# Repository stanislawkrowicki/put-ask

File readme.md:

# 🛠️ PepeBoy

**Portable GameBoy style console. Based on ESP32 microprocessor, 2.8" TFT display, WiFi** 

---

## 📌 Table of Contents
- [🎯 Project Goal](#-project-goal)
- [🔧 Hardware Design](#-hardware-design)
- [💻 Usage](#-usage)
- [🔧 Execution REV1](#-execution)

---

## 🎯 Project Goal

Portable and pocket size console, able to load games from external sd card. Possibility of on-line gameplay via Wi-Fi. Custom PCB board, self-made using CNC milling and UV solder mask paint; 3D printed case.

## 🔧 Hardware Design
The PCB was designed to be produced using a double-sided FR4 PCB blank. Unfortunately, due to the process, every via had to be soldered using copper wire. 

### ESP32 pinout description
#### buttons 
| Button      | Switch id | GPIO  |
|:-----------:|:------:|:-----:|
| Right Button| SW_7   | IO35  |
| Left Button | SW_5   | IO27  |
| Up Button   | SW_4   | IO33  |
| Down Button | SW_6   | IO34  |
| A Button    | SW_8   | IO14  |
| B Button    | SW_3   | IO32  |

#### touch 

| Touch Signal  | Description          | GPIO  |
|:----------:|:--------------------:|:-----:|
| MISO       | Master In Slave Out   | IO19  |
| MOSI       | Master Out Slave In   | IO23  |
| CLK        | Clock                 | IO18  |
| CS_T       | Chip Select           | IO4   |
| T_IRQ      | Interrupt Handling    | IO13  |

#### display
| Display Signal | GPIO  | Description                          |
|:--------------:|:-----:|:-------------------------------------:|
| SPI_CS         | IO21  | Display Chip Select                  |
| SPI_MOSI       | IO23  | Master Out Slave In (data)           |
| SPI_MISO       | IO19  | Master In Slave Out (data)           |
| SPI_CLK        | IO18  | Clock signal                         |
| D_DC           | IO16  | Data/Command control                 |
| D_RST          | IO17  | Display reset signal                 |
| D_LED          | IO22  | Display backlight control            |
#### SD card

| SD Signal  | GPIO  | Description                 |
|:----------:|:-----:|:---------------------------:|
| SD_CS      | IO25  | Chip Select karty SD        |
| SD_CLK     | IO18  | Clock signal                |
| SD_MISO    | IO19  | Master In Slave Out (data)  |
| SD_MOSI    | IO23  | Master Out Slave In (data)  |

#### onePixel 2x2 led matrix
|2x2 LED signal|GPIO|Description|
|:--:|:--:|:--:|
|LED_DIN| IO26|Data in|

####  general SPI
| SPI Signal | GPIO  |
|:----------:|:-----:|
| MISO       | IO19  |
| MOSI       | IO23  |
| CLK        | IO18  |

<!--  -->

### Power Management Unit (IP5306) 
#### read execution paragraph !!!!
The console can be powered remotely using, for example, a 18650 Li-ion battery. Plugging the console into external power through USB-C will power the device and charge the battery. The IP5306 is used according to the typical application from the [datasheet](https://www.datasheetcafe.com/wp-content/uploads/2020/07/IP5306.pdf). We used a one-LED configuration and skipped the KEY_LED (D5 on the datasheet).

## 💻 Usage

Description of how to use the project, e.g., how to start it, available modes, etc.

## 🔧 Execution
The PCB has been *mostly* successfully produced. We will leave a few notes describing our conclusions about what went wrong and what met or exceeded our expectations.

- Power Management Unit Failure: To be honest, I still don’t know exactly what went wrong. The design followed the datasheet, but the IC consistently failed, producing enough heat to desolder itself. After several attempts and considering the project deadline, I abandoned the idea of a remote power supply. If I were to do this again, I’d design a separate board dedicated solely to power management.

- Input-Only Pins (IO35, IO34): These pins lack internal pull-up resistors, and I neglected to include external ones in the design.

- WS2812 Segment Issue: This one’s due to a simple oversight: the collector of the Q1 transistor isn’t pulled up to 5V, which prevents proper operation of the LED segment.

- USB-C Port Soldering Difficulty: The mounting pads for the USB-C connector are too small, making the socket difficult to solder reliably. Larger pads would have made assembly easier.

---

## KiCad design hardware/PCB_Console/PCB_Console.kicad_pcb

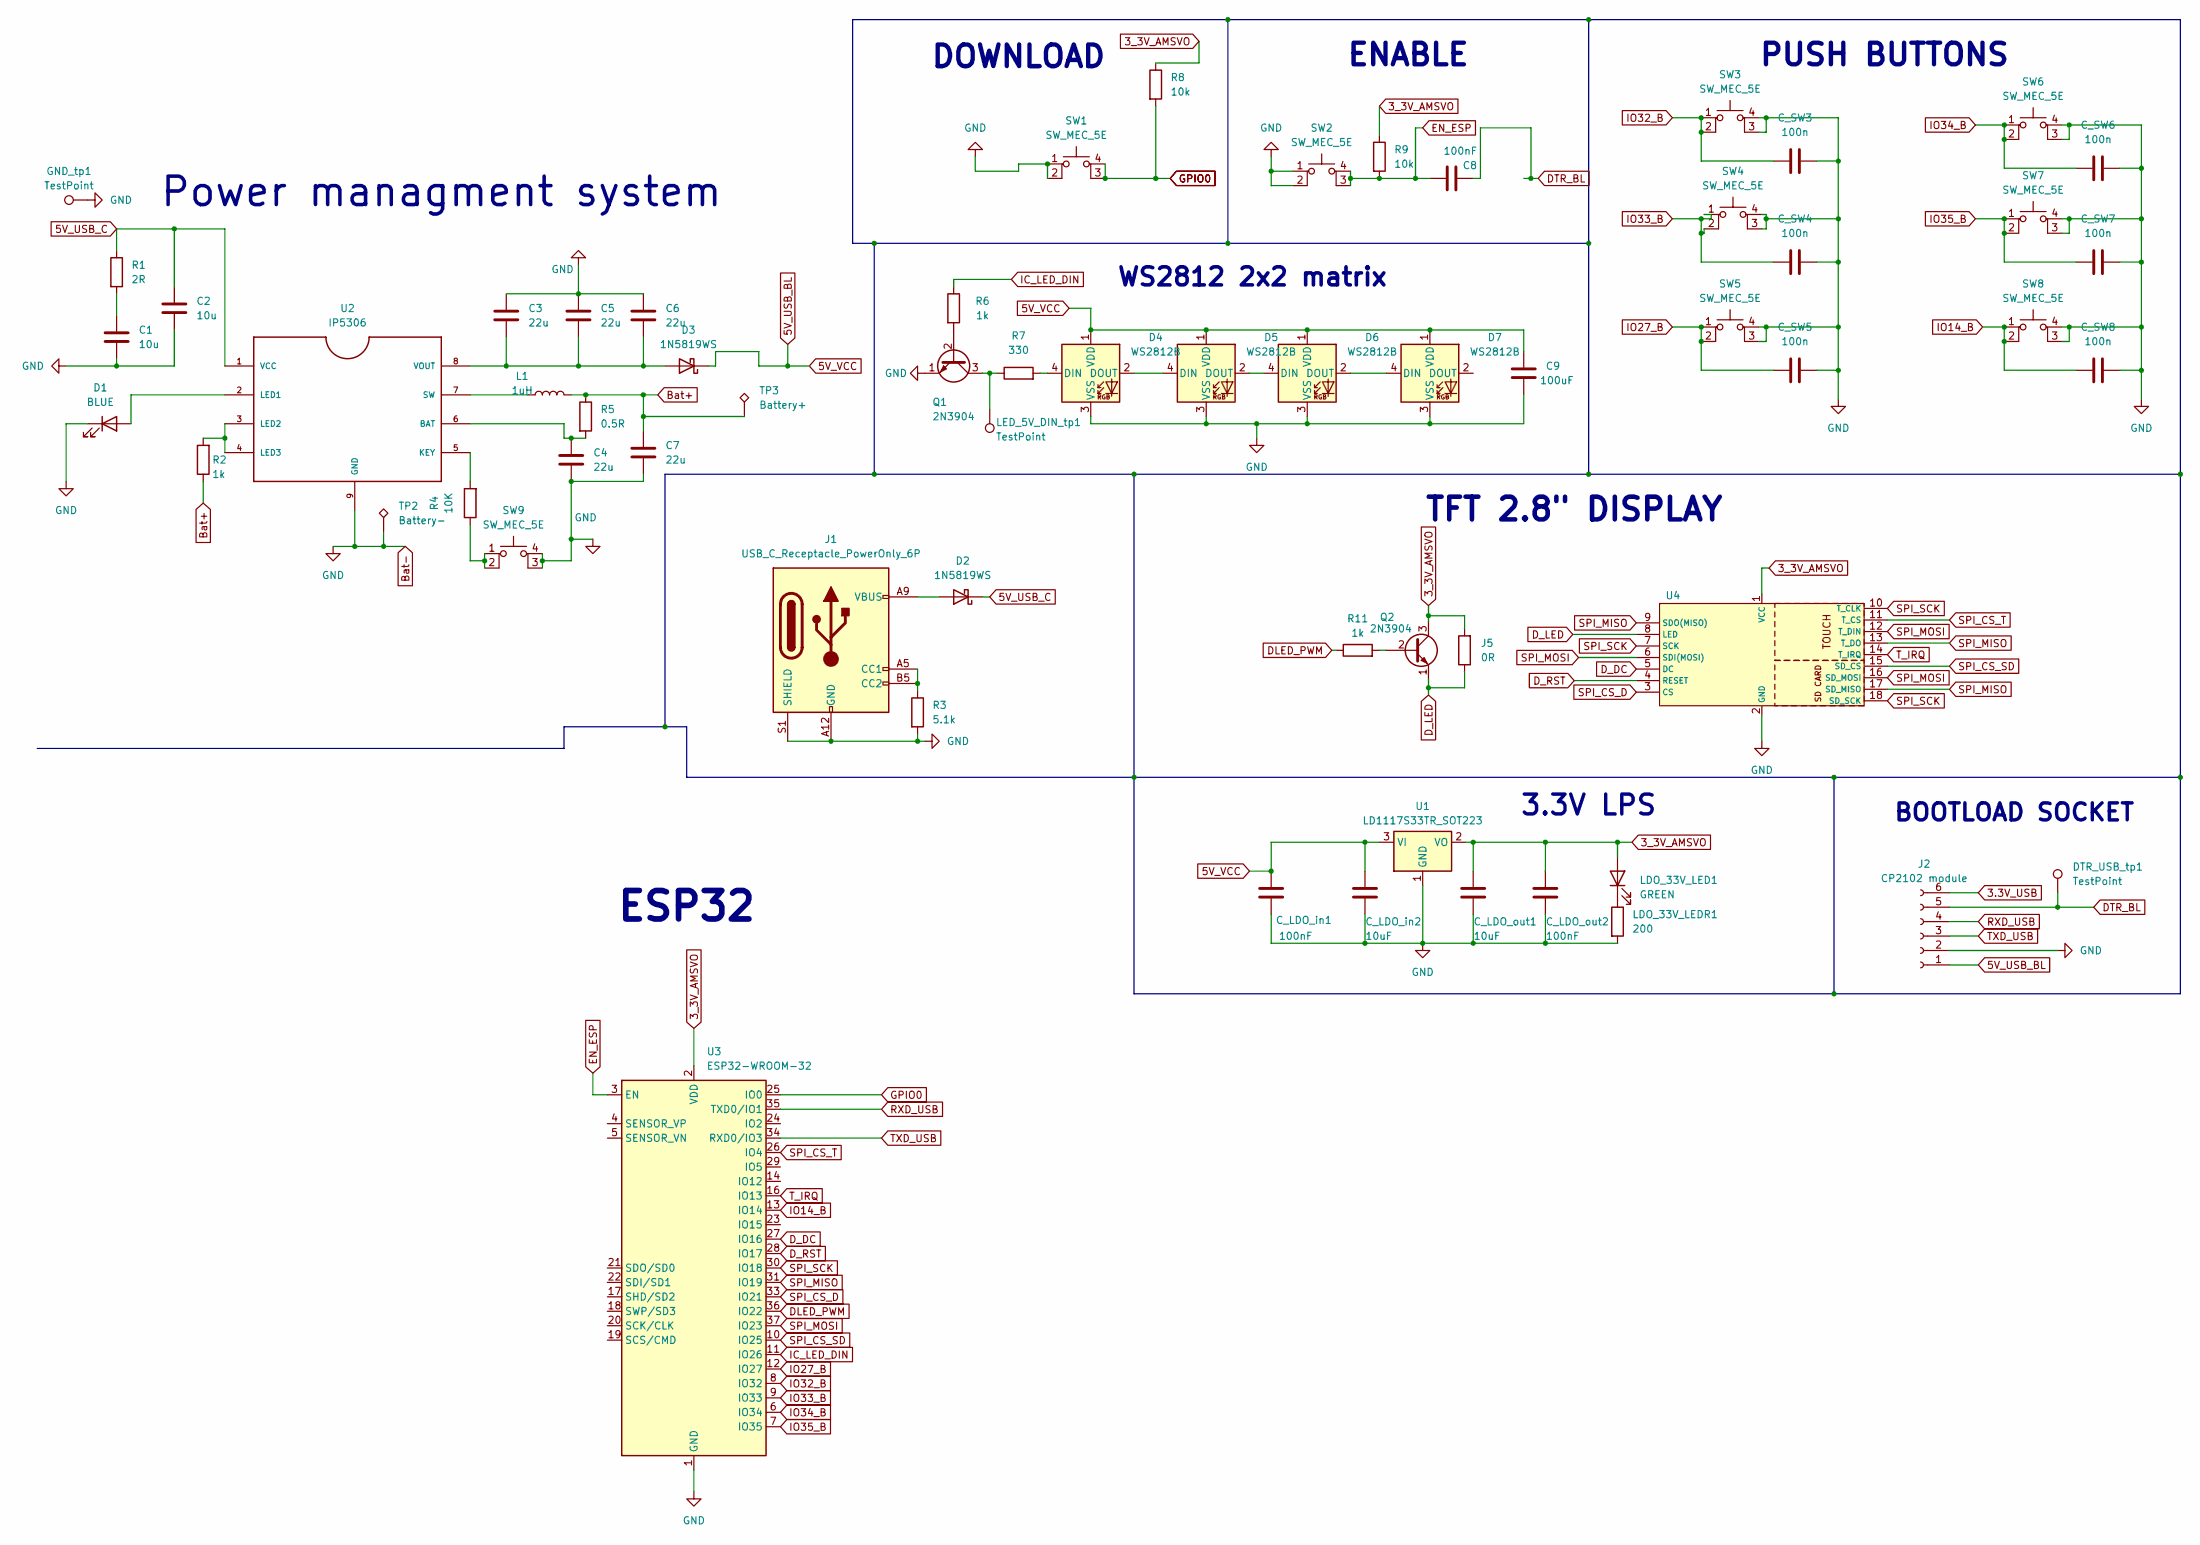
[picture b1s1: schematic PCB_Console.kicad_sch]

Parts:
C1, C2: 10u; C_1206_3216Metric_Pad1.33x1.80mm_HandSolder
C3, C4, C5, C6, C7: 22u; C_1206_3216Metric_Pad1.33x1.80mm_HandSolder
C8: 100nF; C_1206_3216Metric_Pad1.33x1.80mm_HandSolder
C9: 100uF; C_1206_3216Metric_Pad1.33x1.80mm_HandSolder
C_LDO_in1: 100nF; C_1206_3216Metric_Pad1.33x1.80mm_HandSolder
C_LDO_in2: 10uF; C_1206_3216Metric_Pad1.33x1.80mm_HandSolder
C_LDO_out1: 10uF; C_1206_3216Metric_Pad1.33x1.80mm_HandSolder
C_LDO_out2: 100nF; C_1206_3216Metric_Pad1.33x1.80mm_HandSolder
C_SW3, C_SW4, C_SW5, C_SW6, C_SW7, C_SW8: 100n; C_1206_3216Metric_Pad1.33x1.80mm_HandSolder
D1: BLUE; LED_D5.0mm
D2, D3: 1N5819WS; D_0805_2012Metric_Pad1.15x1.40mm_HandSolder
D4, D5, D6, D7: WS2812B; LED_WS2812B_PLCC4_5.0x5.0mm_P3.2mm
DTR_USB_tp1: TestPoint; TestPoint_Pad_D1.0mm
GND_tp1: TestPoint; TestPoint_Pad_D1.5mm
J1: USB_C_Receptacle_PowerOnly_6P; USB_C_Receptacle_GCT_USB4125-xx-x-0190_6P_TopMnt_Horizontal
J2: CP2102 module; PinSocket_1x06_P2.54mm_Vertical
J5: 0R; R_1206_3216Metric_Pad1.30x1.75mm_HandSolder
L1: 1uH; L_Chilisin_BMRB00060650
LDO_33V_LED1: GREEN; LED_D3.0mm
LDO_33V_LEDR1: 200; R_1206_3216Metric_Pad1.30x1.75mm_HandSolder
LED_5V_DIN_tp1: TestPoint; TestPoint_Pad_D1.0mm
Q1, Q2: 2N3904; TO-92_Wide
R1: 2R; R_1206_3216Metric_Pad1.30x1.75mm_HandSolder
R2, R6, R11: 1k; R_1206_3216Metric_Pad1.30x1.75mm_HandSolder
R3: 5.1k; R_1206_3216Metric_Pad1.30x1.75mm_HandSolder
R4: 10K; R_1206_3216Metric_Pad1.30x1.75mm_HandSolder
R5: 0.5R; R_1206_3216Metric_Pad1.30x1.75mm_HandSolder
R7: 330; R_1206_3216Metric_Pad1.30x1.75mm_HandSolder
R8, R9: 10k; R_1206_3216Metric_Pad1.30x1.75mm_HandSolder
SW1, SW2, SW9: SW_MEC_5E; SW_TS04-66-95-BK-100-SMT
SW3, SW4, SW5, SW6, SW7, SW8: SW_MEC_5E; SW_Push_12x12_aliexpress
TP2: Battery-; TestPoint_THTPad_D1.5mm_Drill0.7mm
TP3: Battery+; TestPoint_THTPad_D1.5mm_Drill0.7mm
U1: LD1117S33TR_SOT223; SOT-223-3_TabPin2
U2: IP5306; SOIC9P127_490X600X170L84X42T330X241N
U3: ESP32-WROOM-32
U4: TFT ILI9341

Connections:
3.3V_USB: J2.6
3_3V_AMSVO: C_LDO_out1.1, C_LDO_out2.1, J5.2, LDO_33V_LED1.2 (A), Q2.3 (C), R8.1, R9.1, U1.2 (VO), U3.2 (VDD), U4.1 (VCC)
5V_USB_BL: C9.2, C_LDO_in1.1, C_LDO_in2.1, D3.1 (K), D4.1 (VDD), D5.1 (VDD), D6.1 (VDD), D7.1 (VDD), J2.1, U1.3 (VI)
5V_USB_C: C2.1, D2.1 (K), R1.1, U2.1 (VCC)
Bat+: C7.1, L1.2, R2.1, R5.1, TP3.1
Bat-: C1.2, C2.2, C3.1, C4.2, C5.1, C6.1, C7.2, C9.1, C_LDO_in1.2, C_LDO_in2.2, C_LDO_out1.2, C_LDO_out2.2, C_SW3.1, C_SW4.1, C_SW5.1, C_SW6.1, C_SW7.1, C_SW8.1, D1.1 (K), D4.3 (VSS), D5.3 (VSS), D6.3 (VSS), D7.3 (VSS), GND_tp1.1, J1.A12 (GND), J1.B12 (GND), J1.S1 (SHIELD), J2.2, LDO_33V_LEDR1.2, Q1.1 (E), R3.2, SW1.1, SW1.2, SW2.1, SW2.2, SW3.3 (K), SW3.4 (A), SW4.3 (K), SW4.4 (A), SW5.3 (K), SW5.4 (A), SW6.3 (K), SW6.4 (A), SW7.3 (K), SW7.4 (A), SW8.3 (K), SW8.4 (A), SW9.3 (K), SW9.4 (A), TP2.1, U1.1 (GND), U2.9 (GND), U3.1 (GND), U3.15 (GND), U3.38 (GND), U3.39 (GND), U4.2 (GND)
DLED_PWM: R11.1, U3.36 (IO22)
DTR_BL: C8.2, DTR_USB_tp1.1, J2.5
D_DC: U3.27 (IO16), U4.5 (DC)
D_LED: J5.1, Q2.1 (E), U4.8 (LED)
D_RST: U3.28 (IO17), U4.4 (RESET)
EN_ESP: C8.1, R9.2, SW2.3 (K), SW2.4 (A), U3.3 (EN)
GPIO0: R8.2, SW1.3 (K), SW1.4 (A), U3.25 (IO0)
IC_LED_DIN: R6.1, U3.11 (IO26)
IO14_B: C_SW8.2, SW8.1, SW8.2, U3.13 (IO14)
IO27_B: C_SW5.2, SW5.1, SW5.2, U3.12 (IO27)
IO32_B: C_SW3.2, SW3.1, SW3.2, U3.8 (IO32)
IO33_B: C_SW4.2, SW4.1, SW4.2, U3.9 (IO33)
IO34_B: C_SW6.2, SW6.1, SW6.2, U3.6 (IO34)
IO35_B: C_SW7.2, SW7.1, SW7.2, U3.7 (IO35)
unnamed: C1.1, R1.2
unnamed: D1.2 (A), U2.2 (LED1)
unnamed: D2.2 (A), J1.A9 (VBUS), J1.B9 (VBUS)
unnamed: C3.2, C5.2, C6.2, D3.2 (A), U2.8 (VOUT)
unnamed: D4.4 (DIN), R7.2
unnamed: D4.2 (DOUT), D5.4 (DIN)
unnamed: D5.2 (DOUT), D6.4 (DIN)
unnamed: D6.2 (DOUT), D7.4 (DIN)
unnamed: J1.A5 (CC1), J1.B5 (CC2), R3.1
unnamed: LDO_33V_LED1.1 (K), LDO_33V_LEDR1.1
unnamed: Q1.2 (B), R6.2
unnamed: LED_5V_DIN_tp1.1, Q1.3 (C), R7.1
unnamed: Q2.2 (B), R11.2
unnamed: R4.1, SW9.1, SW9.2
unnamed: C4.1, R5.2, U2.6 (BAT)
unnamed: R4.2, U2.5 (KEY)
unnamed: R2.2, U2.3 (LED2), U2.4 (LED3)
unnamed: L1.1, U2.7 (SW)
RXD_USB: J2.4, U3.35 (TXD0/IO1)
SPI_CS_D: U3.33 (IO21), U4.3 (CS)
SPI_CS_SD: U3.10 (IO25), U4.15 (SD_CS)
SPI_CS_T: U3.26 (IO4), U4.11 (T_CS)
SPI_MISO: U3.31 (IO19), U4.9 (SDO(MISO)), U4.13 (T_DO), U4.17 (SD_MISO)
SPI_MOSI: U3.37 (IO23), U4.6 (SDI(MOSI)), U4.12 (T_DIN), U4.16 (SD_MOSI)
SPI_SCK: U3.30 (IO18), U4.7 (SCK), U4.10 (T_CLK), U4.18 (SD_SCK)
TXD_USB: J2.3, U3.34 (RXD0/IO3)
T_IRQ: U3.16 (IO13), U4.14 (T_IRQ)

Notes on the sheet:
ESP32
PUSH BUTTONS
Power managment system
BOOTLOAD SOCKET
3.3V LPS
TFT 2.8" DISPLAY
DOWNLOAD
WS2812 2x2 matrix
ENABLE

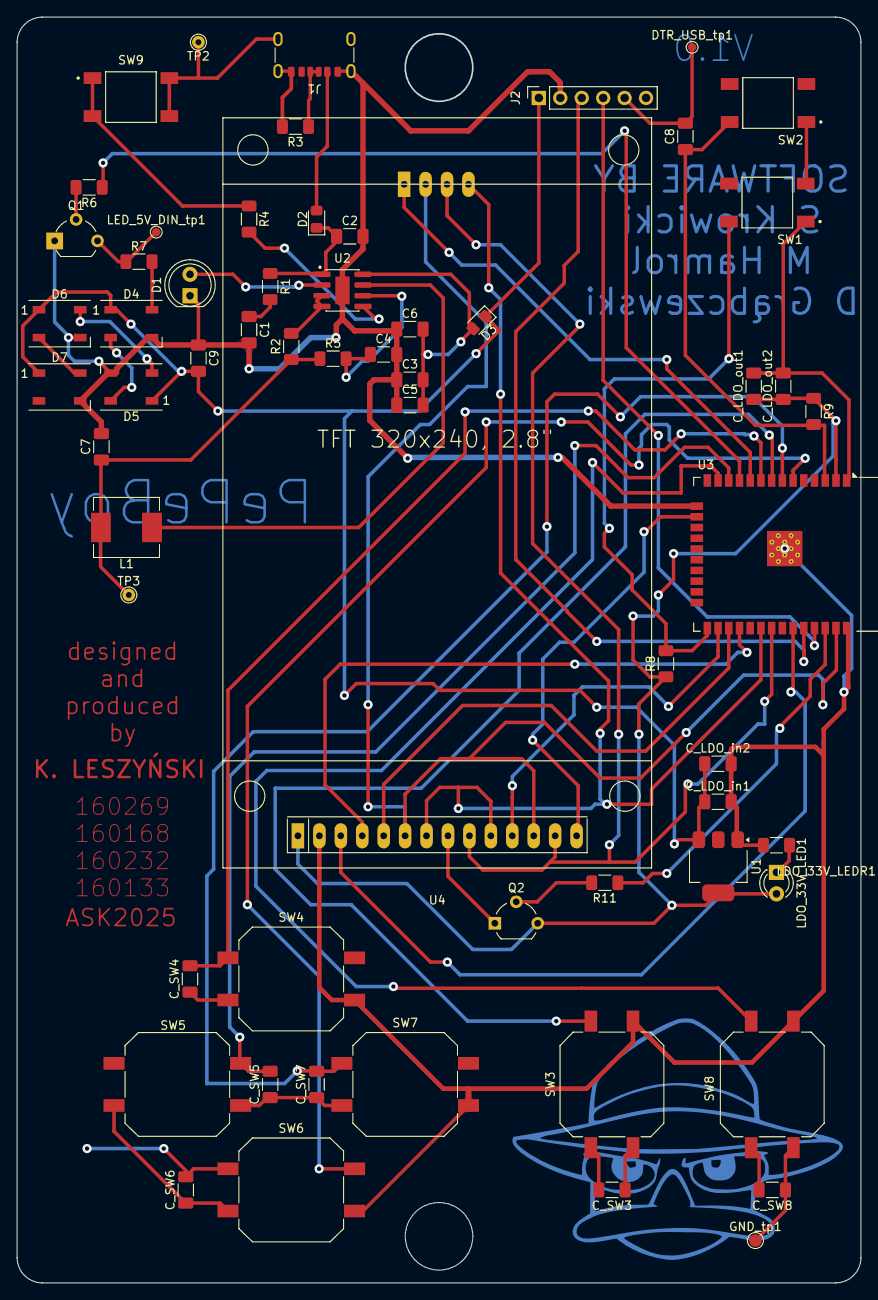
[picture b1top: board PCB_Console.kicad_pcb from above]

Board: 2 copper layers, 100.0 x 150.0 mm, 61 parts (0 on the bottom side), 46 nets.

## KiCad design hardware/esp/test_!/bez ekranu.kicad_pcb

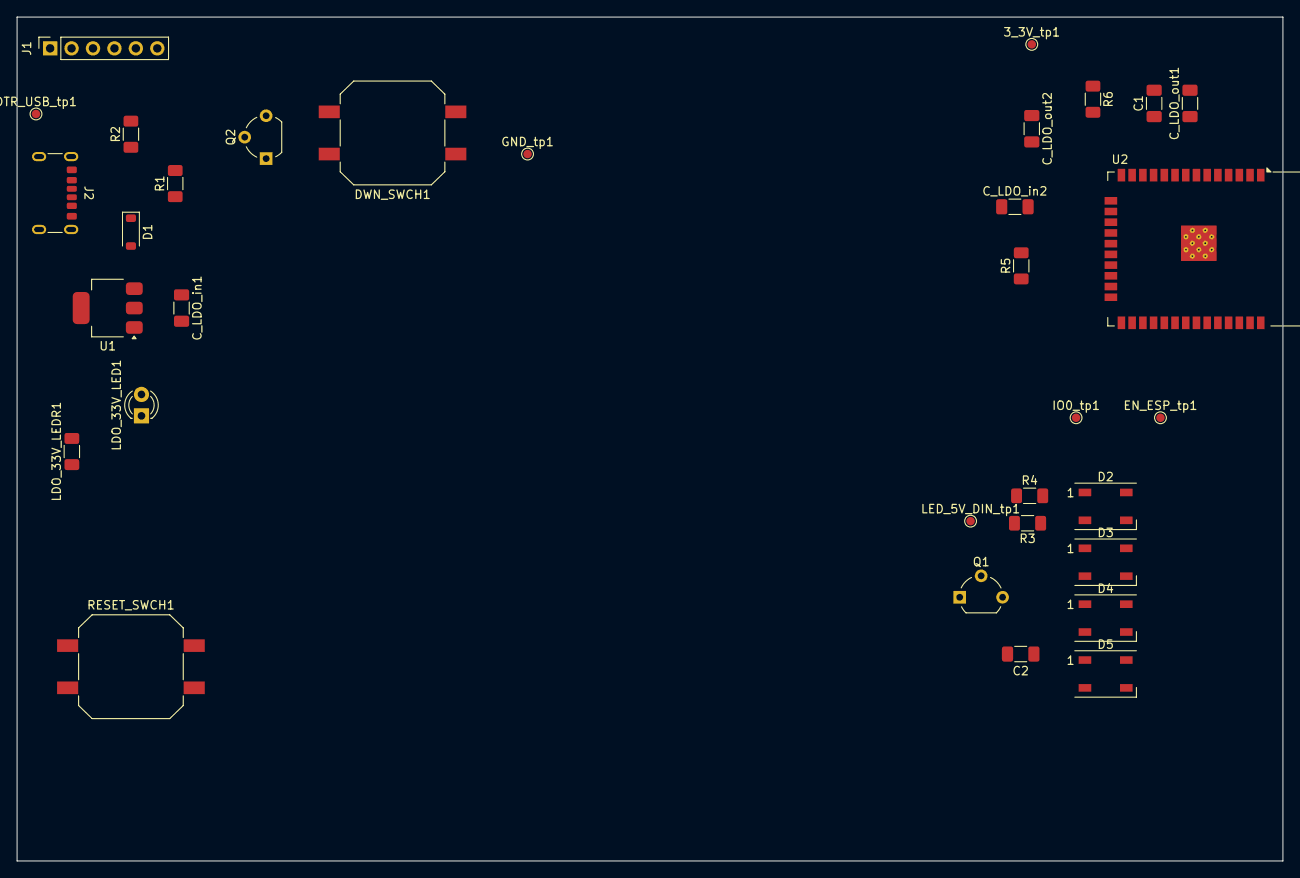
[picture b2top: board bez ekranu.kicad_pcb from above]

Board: 2 copper layers, 150.0 x 100.0 mm, 33 parts (0 on the bottom side), 17 nets, no tracks yet.

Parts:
3_3V_tp1: TestPoint; TestPoint_Pad_D1.0mm
C1: 100nF; C_1206_3216Metric_Pad1.33x1.80mm_HandSolder
C2: 100uF; C_1206_3216Metric_Pad1.33x1.80mm_HandSolder
C_LDO_in1: 100nF; C_1206_3216Metric_Pad1.33x1.80mm_HandSolder
C_LDO_in2: 10uF; C_1206_3216Metric_Pad1.33x1.80mm_HandSolder
C_LDO_out1: 10uF; C_1206_3216Metric_Pad1.33x1.80mm_HandSolder
C_LDO_out2: 100nF; C_1206_3216Metric_Pad1.33x1.80mm_HandSolder
D1: 1N5819WS; D_SOD-123
D2, D3, D4, D5: WS2812B; LED_WS2812B_PLCC4_5.0x5.0mm_P3.2mm
DTR_USB_tp1: TestPoint; TestPoint_Pad_D1.0mm
DWN_SWCH1: SW_Push_Dual; SW_Push_12x12_aliexpress
EN_ESP_tp1: TestPoint; TestPoint_Pad_D1.0mm
GND_tp1: TestPoint; TestPoint_Pad_D1.0mm
IO0_tp1: TestPoint; TestPoint_Pad_D1.0mm
J1: CP2102 module; PinSocket_1x06_P2.54mm_Vertical
J2: USB_C_Receptacle_PowerOnly_6P; USB_C_Receptacle_GCT_USB4125-xx-x-0190_6P_TopMnt_Horizontal
LDO_33V_LED1: LED; LED_D3.0mm
LDO_33V_LEDR1: 150; R_1206_3216Metric_Pad1.30x1.75mm_HandSolder
LED_5V_DIN_tp1: TestPoint; TestPoint_Pad_D1.0mm
Q1, Q2: 2N3904; TO-92_Wide
R1: 5.1k; R_1206_3216Metric_Pad1.30x1.75mm_HandSolder
R2, R3: 1k; R_1206_3216Metric_Pad1.30x1.75mm_HandSolder
R4: 330; R_1206_3216Metric_Pad1.30x1.75mm_HandSolder
R5, R6: 10k; R_1206_3216Metric_Pad1.30x1.75mm_HandSolder
RESET_SWCH1: SW_Push_Dual; SW_Push_12x12_aliexpress
U1: LD1117S33TR_SOT223; SOT-223-3_TabPin2
U2: ESP32-WROOM-32

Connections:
3_3V_AMSVO: 3_3V_tp1.1, C_LDO_out1.1, C_LDO_out2.1, LDO_33V_LED1.2 (A), R5.1, R6.1, U1.2 (VO), U2.2 (VDD)
5V_USB_BL: D1.1 (K), J1.1, J2.A9 (VBUS), J2.B9 (VBUS)
5V_VCC: C2.2, C_LDO_in1.1, C_LDO_in2.1, D1.2 (A), D2.1 (VDD), D3.1 (VDD), D4.1 (VDD), D5.1 (VDD), U1.3 (VI)
DTR_BL: C1.2, DTR_USB_tp1.1, J1.5, R2.1
EN_ESP: C1.1, EN_ESP_tp1.1, R6.2, RESET_SWCH1.2, RESET_SWCH1.4, U2.3 (EN)
GND: C2.1, C_LDO_in1.2, C_LDO_in2.2, C_LDO_out1.2, C_LDO_out2.2, D2.3 (VSS), D3.3 (VSS), D4.3 (VSS), D5.3 (VSS), DWN_SWCH1.1, DWN_SWCH1.3, GND_tp1.1, J1.2, J2.A12 (GND), J2.B12 (GND), J2.S1 (SHIELD), LDO_33V_LEDR1.2, Q1.1 (E), Q2.1 (E), R1.2, RESET_SWCH1.1, RESET_SWCH1.3, U1.1 (GND), U2.1 (GND), U2.15 (GND), U2.38 (GND), U2.39 (GND)
GPIO0: DWN_SWCH1.2, DWN_SWCH1.4, IO0_tp1.1, Q2.3 (C), R5.2, U2.25 (IO0)
IC_LED_DIN: R3.1, U2.7 (IO35), U2.27 (IO16)
unnamed: D2.4 (DIN), R4.2
unnamed: D2.2 (DOUT), D3.4 (DIN)
unnamed: D3.2 (DOUT), D4.4 (DIN)
unnamed: D4.2 (DOUT), D5.4 (DIN)
unnamed: J2.A5 (CC1), J2.B5 (CC2), R1.1
unnamed: LDO_33V_LED1.1 (K), LDO_33V_LEDR1.1
unnamed: Q1.2 (B), R3.2
unnamed: LED_5V_DIN_tp1.1, Q1.3 (C), R4.1
unnamed: Q2.2 (B), R2.2

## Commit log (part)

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2025-04-01 może tym razem wszystkiego niezepsuje?
2025-04-01 adding directory for clean estetiques
2025-04-01 renamed kicad files
2025-04-01 got rid off unnecessary backups
2025-04-01 readme template
2025-04-02 readme edited, gitignore added few lines
2025-04-02 dodano przyciski, poprawione biblioteki
2025-04-06 display connected to esp, pinout checked
2025-04-06 deleted unnecessery back-ups; making schematic more modular, easier to read
2025-04-13 zaczynam routing, zaczynam sie martwic ze ten projekt jest awykonalny w dostepnej technologi
2025-04-16 routing and placment, few edits on schematics
2025-04-16 routing next step
2025-04-17 routing czesc dalsza, power manager system wmiare polaczony
2025-04-19 routing od nowa na 2 warstwach
2025-04-20 routing on 2l done, need to check, text and logo added
2025-04-24 readme pinout description added
2025-04-25 readme power system added
2025-04-25 fajnie jest zobaczyc czy literowek nie ma przed commitem a nie po
2025-04-29 OTAServer base
2025-04-29 Add wifi_secrets.h
2025-04-29 Stop tracking wifi_secrets.h, add root .vscode to .gitignore
2025-04-29 Working OTA upload ESP32 firmware
2025-04-29 Example update via Python
2025-04-29 Send 200 OK response after updating
2025-04-29 Rebuild updated OTA library
2025-05-03 full basic game translation from non-TFT screen
2025-05-05 Ignore .vscode in all .gitignores
2025-05-05 Add example wifi_secrets
2025-05-05 Basic launcher layout
2025-05-05 Change up the folder structure a bit; sent game info from server; add a function that moves thumbnails from games sources to web
2025-05-06 Get mocked devices from backend
2025-05-06 New layout for game view, mock game start
2025-05-06 Rename js & css files for index
2025-05-06 Add hover effect for game images on main page
2025-05-06 Add text inside game image on index; hover effect
2025-05-09 Flickering correction
2025-05-11 Update readme.md wrong pin number TFT SPI RST
2025-05-11 pinout fixed, now it is according to readme and PCB
2025-05-13 pcb that was produced
2025-05-13 case stl models added
2025-05-13 readme few lines added
2025-05-15 Games can be ran through the launcher
2025-05-15 Discover devices before running the UI; refresh devices in game tab
2025-05-15 Stop tracking games/
2025-05-15 Add a script that compiles all the games and moves the prepared firmwares to pepelauncher/games
2025-05-16 Add the rest of the games, disable button while programming, fix discovery only working the first time
2025-05-16 Add animation while the game is loading
2025-05-16 Add `Go back` button to game view
2025-05-16 Add custom font
2025-05-16 Implement fallbacks to different browsers if there is no Chrome
2025-05-16 PepeLauncher (#3)
2025-05-16 pull up resistors added; level shifter fixed-> tested using sim LTspice
2025-05-17 Make WiFi connecting process non-blocking
2025-05-17 Add --clean flag to games builder that cleans cache before compiling
2025-05-18 Add images for games
2025-05-19 Fix pinouts in games
